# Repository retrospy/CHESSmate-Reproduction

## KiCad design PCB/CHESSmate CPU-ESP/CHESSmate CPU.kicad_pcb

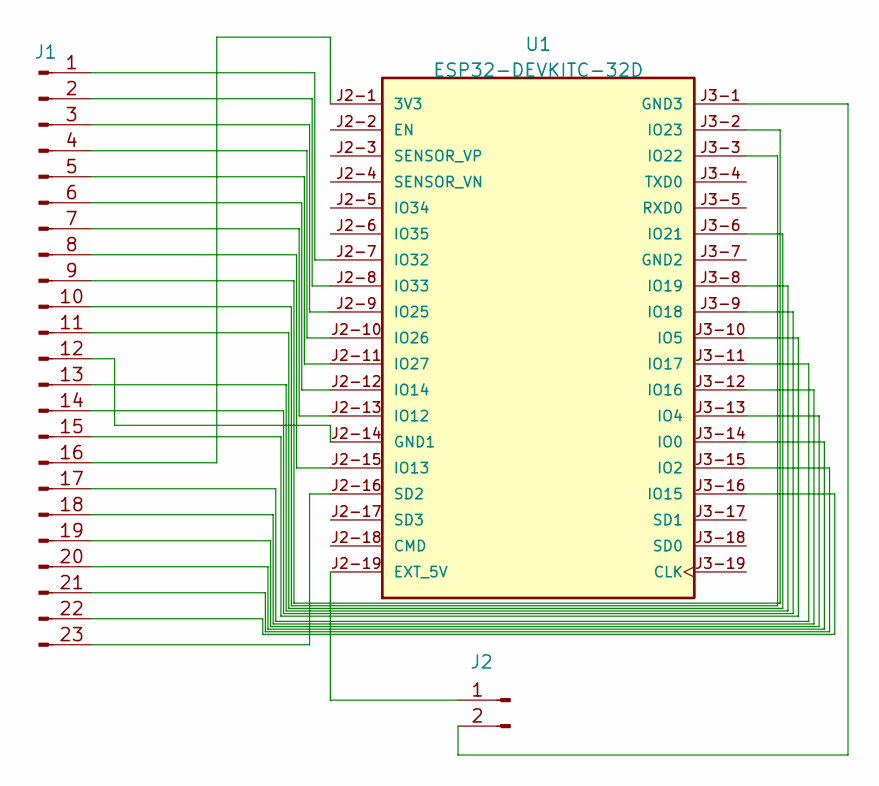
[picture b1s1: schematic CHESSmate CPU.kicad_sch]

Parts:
J1: Conn_01x22_Pin; PinHeader_1x23_P2.54mm_Vertical
J2: Conn_01x02_Pin; PinHeader_1x02_P2.54mm_Vertical
U1: ESP32-DEVKITC-32D; MODULE_ESP32-DEVKITC-32D; PARTREV V4

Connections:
unnamed: J1.1, U1.J2-7 (IO32)
unnamed: J1.2, U1.J2-8 (IO33)
unnamed: J1.3, U1.J2-9 (IO25)
unnamed: J1.4, U1.J2-10 (IO26)
unnamed: J1.5, U1.J2-11 (IO27)
unnamed: J1.6, U1.J2-12 (IO14)
unnamed: J1.7, U1.J2-13 (IO12)
unnamed: J1.8, U1.J2-15 (IO13)
unnamed: J1.9, U1.J3-2 (IO23)
unnamed: J1.10, U1.J3-3 (IO22)
unnamed: J1.11, U1.J3-6 (IO21)
unnamed: J1.12, U1.J2-14 (GND1)
unnamed: J1.13, U1.J3-8 (IO19)
unnamed: J1.14, U1.J3-9 (IO18)
unnamed: J1.15, U1.J3-10 (IO5)
unnamed: J1.16, U1.J2-1 (3V3)
unnamed: J1.17, U1.J3-11 (IO17)
unnamed: J1.18, U1.J3-12 (IO16)
unnamed: J1.19, U1.J3-13 (IO4)
unnamed: J1.20, U1.J3-14 (IO0)
unnamed: J1.21, U1.J3-15 (IO2)
unnamed: J1.22, U1.J3-16 (IO15)
unnamed: J1.23, U1.J2-16 (SD2)
unnamed: J2.1, U1.J2-19 (EXT_5V)
unnamed: J2.2, U1.J3-1 (GND3)

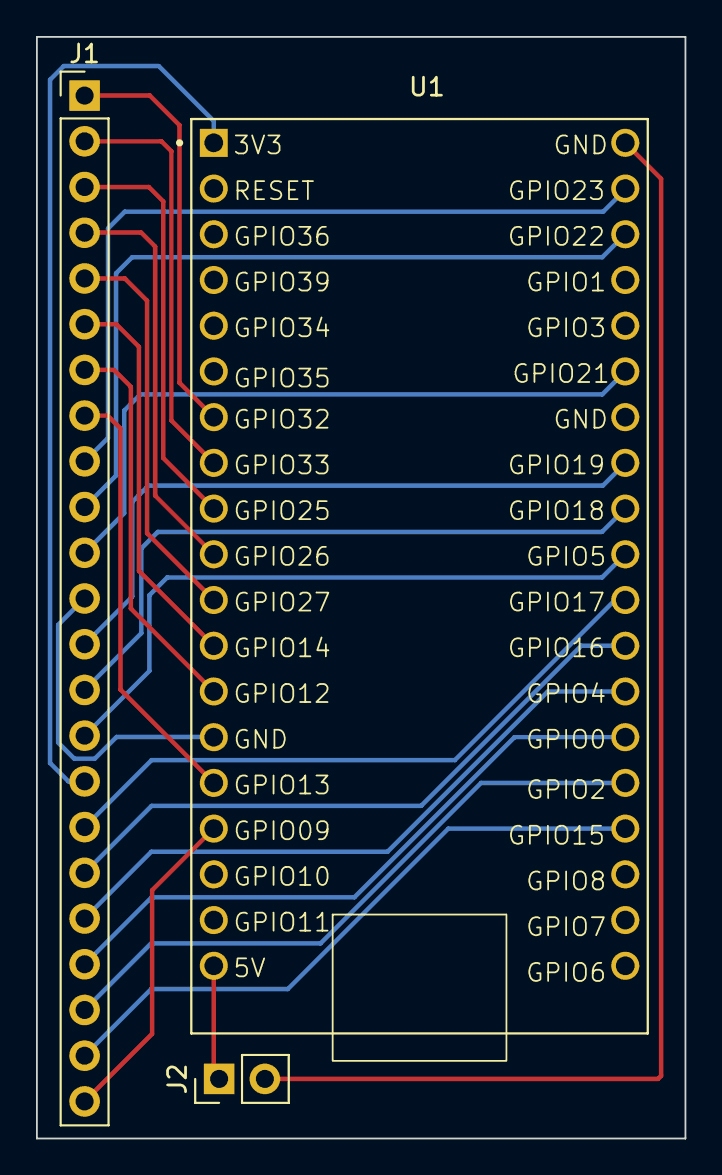
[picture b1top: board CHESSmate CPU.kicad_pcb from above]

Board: 2 copper layers, 36.0 x 61.2 mm, 3 parts (0 on the bottom side), 25 nets.

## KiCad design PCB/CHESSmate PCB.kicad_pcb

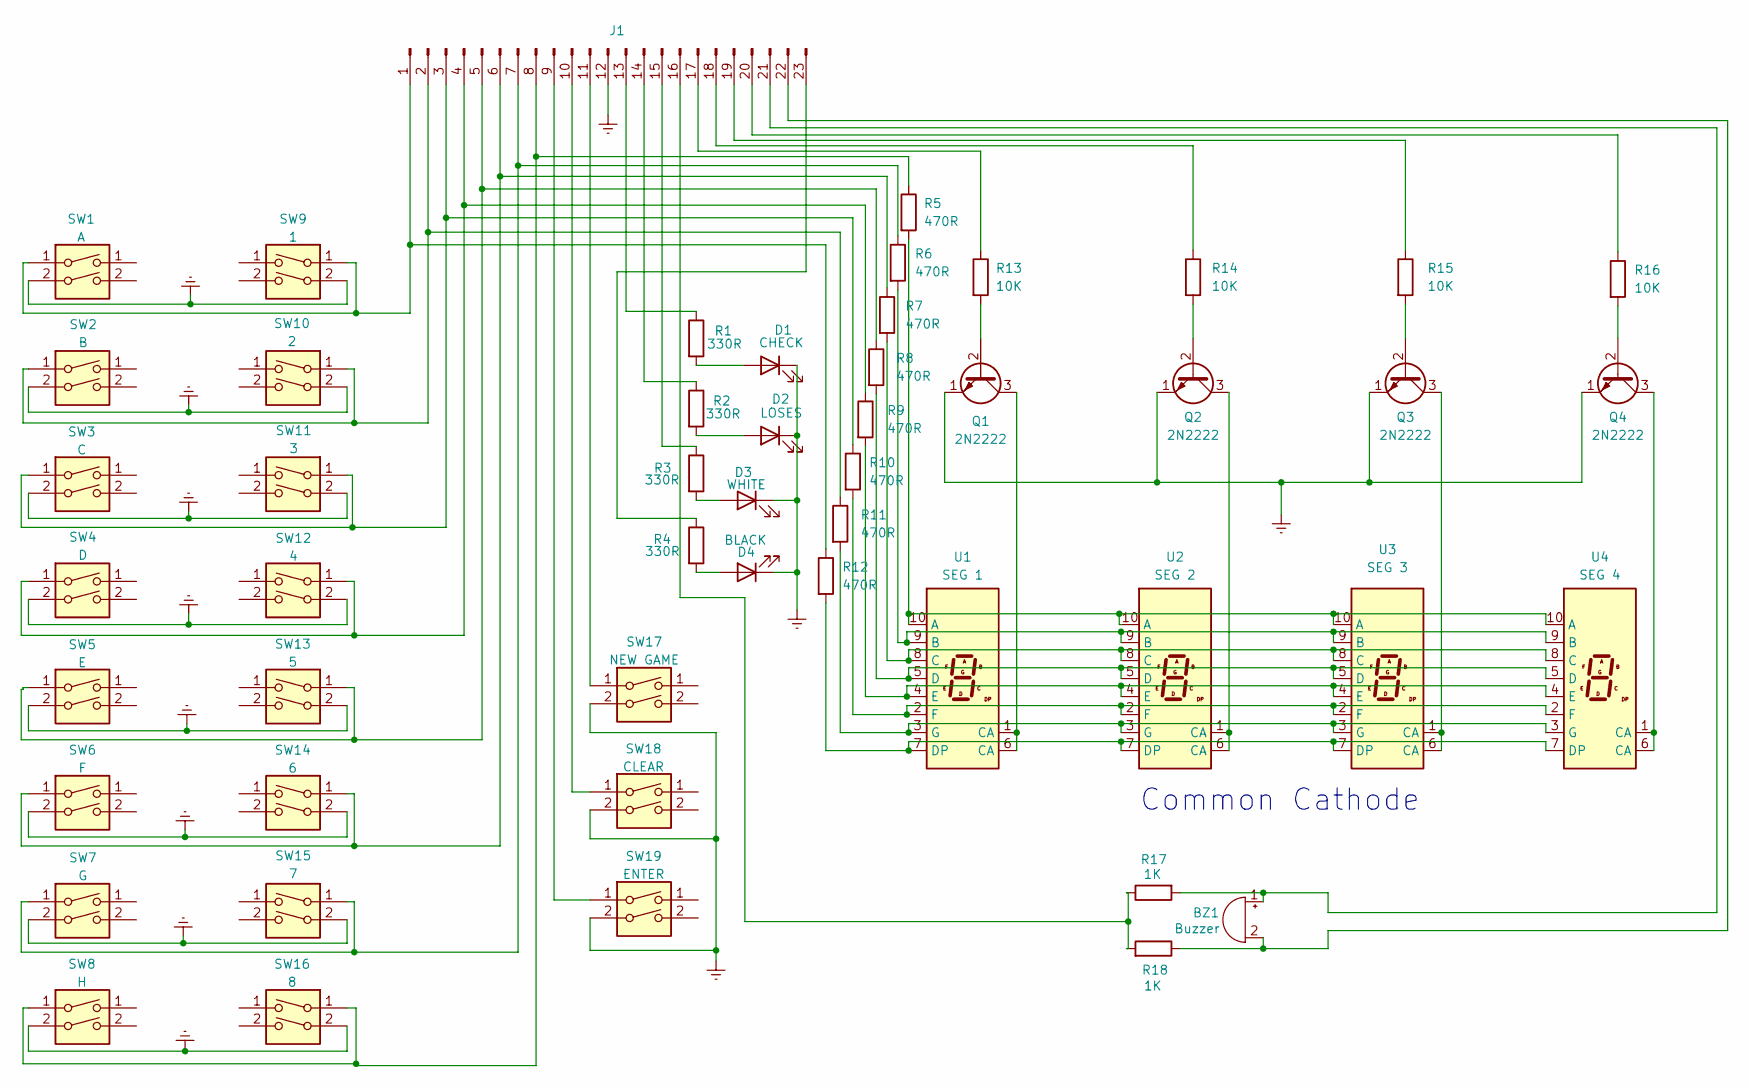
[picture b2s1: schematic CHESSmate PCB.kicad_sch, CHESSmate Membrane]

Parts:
BZ1: Buzzer; Buzzer_12x9.5RM7.6
D1: CHECK; LED_D5.0mm
D2: LOSES; LED_D5.0mm
D3: WHITE; LED_D5.0mm
D4: BLACK; LED_D5.0mm
J1: PinHeader_1x23_P2.54mm_Vertical
Q1, Q2, Q3, Q4: 2N2222; TO-92_Inline
R1, R2, R3, R4: 330R; R_Axial_DIN0207_L6.3mm_D2.5mm_P10.16mm_Horizontal
R5, R6, R7, R8, R9, R10, R11, R12: 470R; R_Axial_DIN0207_L6.3mm_D2.5mm_P10.16mm_Horizontal
R13, R14, R15, R16: 10K; R_Axial_DIN0207_L6.3mm_D2.5mm_P10.16mm_Horizontal
R17, R18: 1K; R_Axial_DIN0207_L6.3mm_D2.5mm_P10.16mm_Horizontal
SW1: A; SW_PUSH-12mm_Wuerth-430476085716
SW2: B; SW_PUSH-12mm_Wuerth-430476085716
SW3: C; SW_PUSH-12mm_Wuerth-430476085716
SW4: D; SW_PUSH-12mm_Wuerth-430476085716
SW5: E; SW_PUSH-12mm_Wuerth-430476085716
SW6: F; SW_PUSH-12mm_Wuerth-430476085716
SW7: G; SW_PUSH-12mm_Wuerth-430476085716
SW8: H; SW_PUSH-12mm_Wuerth-430476085716
SW9: 1; SW_PUSH-12mm_Wuerth-430476085716
SW10: 2; SW_PUSH-12mm_Wuerth-430476085716
SW11: 3; SW_PUSH-12mm_Wuerth-430476085716
SW12: 4; SW_PUSH-12mm_Wuerth-430476085716
SW13: 5; SW_PUSH-12mm_Wuerth-430476085716
SW14: 6; SW_PUSH-12mm_Wuerth-430476085716
SW15: 7; SW_PUSH-12mm_Wuerth-430476085716
SW16: 8; SW_PUSH-12mm_Wuerth-430476085716
SW17: NEW GAME; SW_PUSH-12mm
SW18: CLEAR; SW_PUSH-12mm_Wuerth-430476085716
SW19: ENTER; SW_PUSH-12mm_Wuerth-430476085716
U1: SEG 1; HDSP-A151
U2: SEG 2; HDSP-A151
U3: SEG 3; HDSP-A151
U4: SEG 4; HDSP-A151

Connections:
GNDREF: D1.1 (K), D2.1 (K), D3.1 (K), D4.1 (K), J1.12, Q1.1 (E), Q2.1 (E), Q3.1 (E), Q4.1 (E), SW1.2, SW2.2, SW3.2, SW4.2, SW5.2, SW6.2, SW7.2, SW8.2, SW9.2 (`), SW10.2, SW11.2, SW12.2, SW13.2, SW14.2, SW15.2, SW16.2, SW17.2, SW18.2, SW19.2
unnamed: BZ1.2 (+), J1.22, R18.1
unnamed: BZ1.1 (-), J1.21, R17.2
unnamed: D1.2 (A), R1.2
unnamed: D2.2 (A), R2.2
unnamed: D3.2 (A), R3.2
unnamed: D4.2 (A), R4.2
unnamed: J1.1, R12.1, SW1.1, SW9.1
unnamed: J1.2, R11.1, SW2.1, SW10.1
unnamed: J1.3, R10.1, SW3.1, SW11.1
unnamed: J1.4, R9.1, SW4.1, SW12.1
unnamed: J1.5, R8.1, SW5.1, SW13.1
unnamed: J1.6, R7.1, SW6.1, SW14.1
unnamed: J1.7, R6.1, SW7.1, SW15.1
unnamed: J1.8, R5.1, SW8.1, SW16.1
unnamed: J1.9, SW19.1
unnamed: J1.10, SW18.1
unnamed: J1.11, SW17.1
unnamed: J1.13, R1.1
unnamed: J1.14, R2.1
unnamed: J1.15, R3.1
unnamed: J1.16, R17.1, R18.2
unnamed: J1.17, R13.1
unnamed: J1.18, R14.1
unnamed: J1.19, R15.1
unnamed: J1.20, R16.1
unnamed: J1.23, R4.1
unnamed: Q1.2 (B), R13.2
unnamed: Q1.3 (C), U1.1 (CA), U1.6 (CA)
unnamed: Q2.2 (B), R14.2
unnamed: Q2.3 (C), U2.1 (CA), U2.6 (CA)
unnamed: Q3.2 (B), R15.2
unnamed: Q3.3 (C), U3.1 (CA), U3.6 (CA)
unnamed: Q4.2 (B), R16.2
unnamed: Q4.3 (C), U4.1 (CA), U4.6 (CA)
unnamed: R5.2, U1.10 (A), U2.10 (A), U3.10 (A), U4.10 (A)
unnamed: R6.2, U1.9 (B), U2.9 (B), U3.9 (B), U4.9 (B)
unnamed: R7.2, U1.8 (C), U2.8 (C), U3.8 (C), U4.8 (C)
unnamed: R8.2, U1.5 (D), U2.5 (D), U3.5 (D), U4.5 (D)
unnamed: R12.2, U1.7 (DP), U2.7 (DP), U3.7 (DP), U4.7 (DP)
unnamed: R9.2, U1.4 (E), U2.4 (E), U3.4 (E), U4.4 (E)
unnamed: R10.2, U1.2 (F), U2.2 (F), U3.2 (F), U4.2 (F)
unnamed: R11.2, U1.3 (G), U2.3 (G), U3.3 (G), U4.3 (G)

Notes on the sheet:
Common Cathode

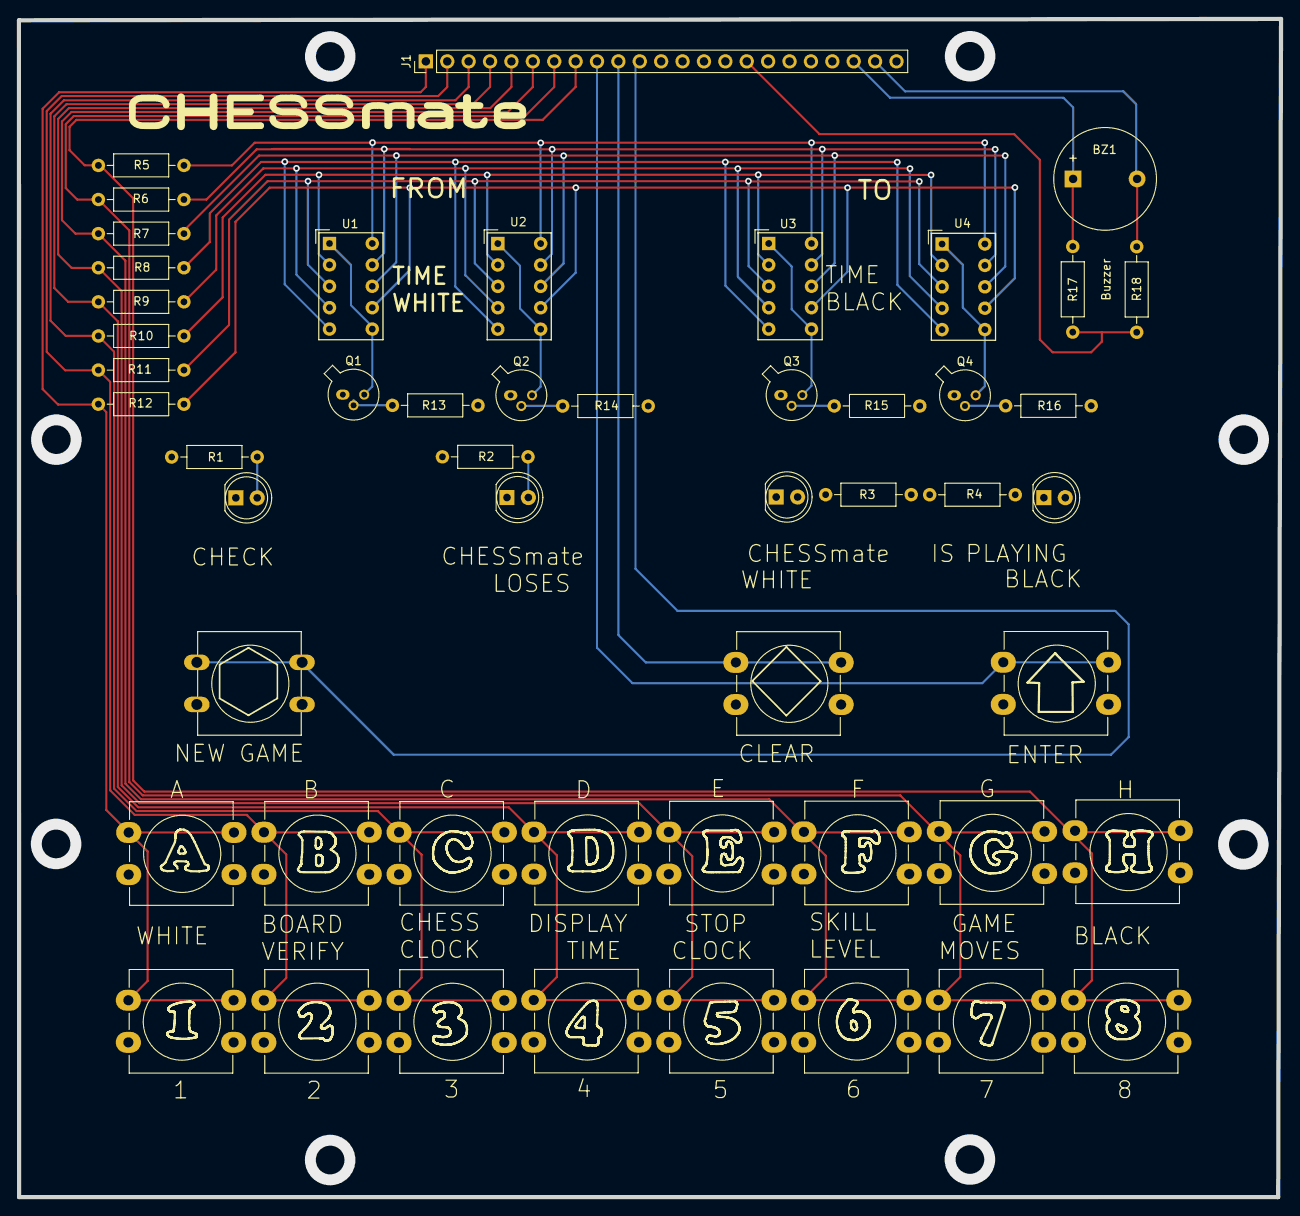
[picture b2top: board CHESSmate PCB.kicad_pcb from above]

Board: 4 copper layers, 149.8 x 139.9 mm, 51 parts (0 on the bottom side), 43 nets.

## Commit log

2024-08-03 23 pin CPU connector
    This doesn't work because you can't use GPIO6, so I designed a new CPU board with a Pi Pico
2024-08-03 Updated Fabrication files
2024-08-03 Seperated the CPU into an ESP version and Pico Version
2024-08-03 Removing unneeded files
2024-08-10 Updated firmware
